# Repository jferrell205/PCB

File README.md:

# PCB
Collection of custom PCBs

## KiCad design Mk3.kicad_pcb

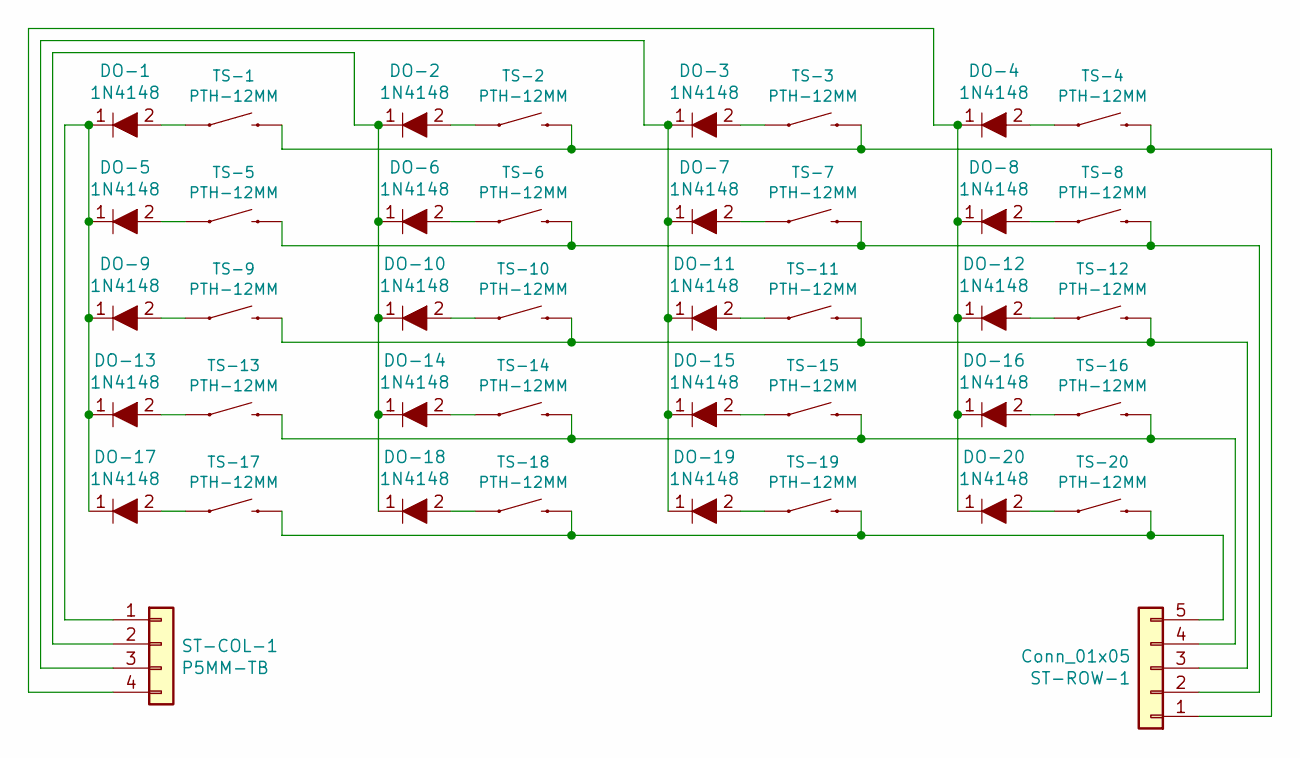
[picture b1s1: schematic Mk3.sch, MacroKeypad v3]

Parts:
DO-1, DO-2, DO-3, DO-4, DO-5, DO-6, DO-7, DO-8, DO-9, DO-10, DO-11, DO-12, DO-13, DO-14, DO-15, DO-16, DO-17, DO-18, DO-19, DO-20: 1N4148; Diode_1N4148_Back; MPN 1N4148; Digi-Key_PN 1N4148FS-ND
ST-COL-1: P5MM-TB; Term_Block_1x4_P5mm
ST-ROW-1: Conn_01x05; Term_Block_1x5_P5mm
TS-1, TS-2, TS-3, TS-4, TS-5, TS-6, TS-7, TS-8, TS-9, TS-10, TS-11, TS-12, TS-13, TS-14, TS-15, TS-16, TS-17, TS-18, TS-19, TS-20: PTH-12MM; TACTILE_SWITCH_PTH_12MM

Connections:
unnamed: DO-1.1, DO-5.1, DO-9.1, DO-13.1, DO-17.1, ST-COL-1.1
unnamed: DO-1.2, TS-1.1
unnamed: DO-2.2, TS-2.1
unnamed: DO-3.2, TS-3.1
unnamed: DO-4.2, TS-4.1
unnamed: DO-5.2, TS-5.1
unnamed: DO-6.2, TS-6.1
unnamed: DO-7.2, TS-7.1
unnamed: DO-8.2, TS-8.1
unnamed: DO-9.2, TS-9.1
unnamed: DO-2.1, DO-6.1, DO-10.1, DO-14.1, DO-18.1, ST-COL-1.2
unnamed: DO-10.2, TS-10.1
unnamed: DO-3.1, DO-7.1, DO-11.1, DO-15.1, DO-19.1, ST-COL-1.3
unnamed: DO-11.2, TS-11.1
unnamed: DO-4.1, DO-8.1, DO-12.1, DO-16.1, DO-20.1, ST-COL-1.4
unnamed: DO-12.2, TS-12.1
unnamed: DO-13.2, TS-13.1
unnamed: DO-14.2, TS-14.1
unnamed: DO-15.2, TS-15.1
unnamed: DO-16.2, TS-16.1
unnamed: DO-17.2, TS-17.1
unnamed: DO-18.2, TS-18.1
unnamed: DO-19.2, TS-19.1
unnamed: DO-20.2, TS-20.1
unnamed: ST-ROW-1.1, TS-1.3 (2), TS-2.3 (2), TS-3.3 (2), TS-4.3 (2)
unnamed: ST-ROW-1.2, TS-5.3 (2), TS-6.3 (2), TS-7.3 (2), TS-8.3 (2)
unnamed: ST-ROW-1.3, TS-9.3 (2), TS-10.3 (2), TS-11.3 (2), TS-12.3 (2)
unnamed: ST-ROW-1.4, TS-13.3 (2), TS-14.3 (2), TS-15.3 (2), TS-16.3 (2)
unnamed: ST-ROW-1.5, TS-17.3 (2), TS-18.3 (2), TS-19.3 (2), TS-20.3 (2)

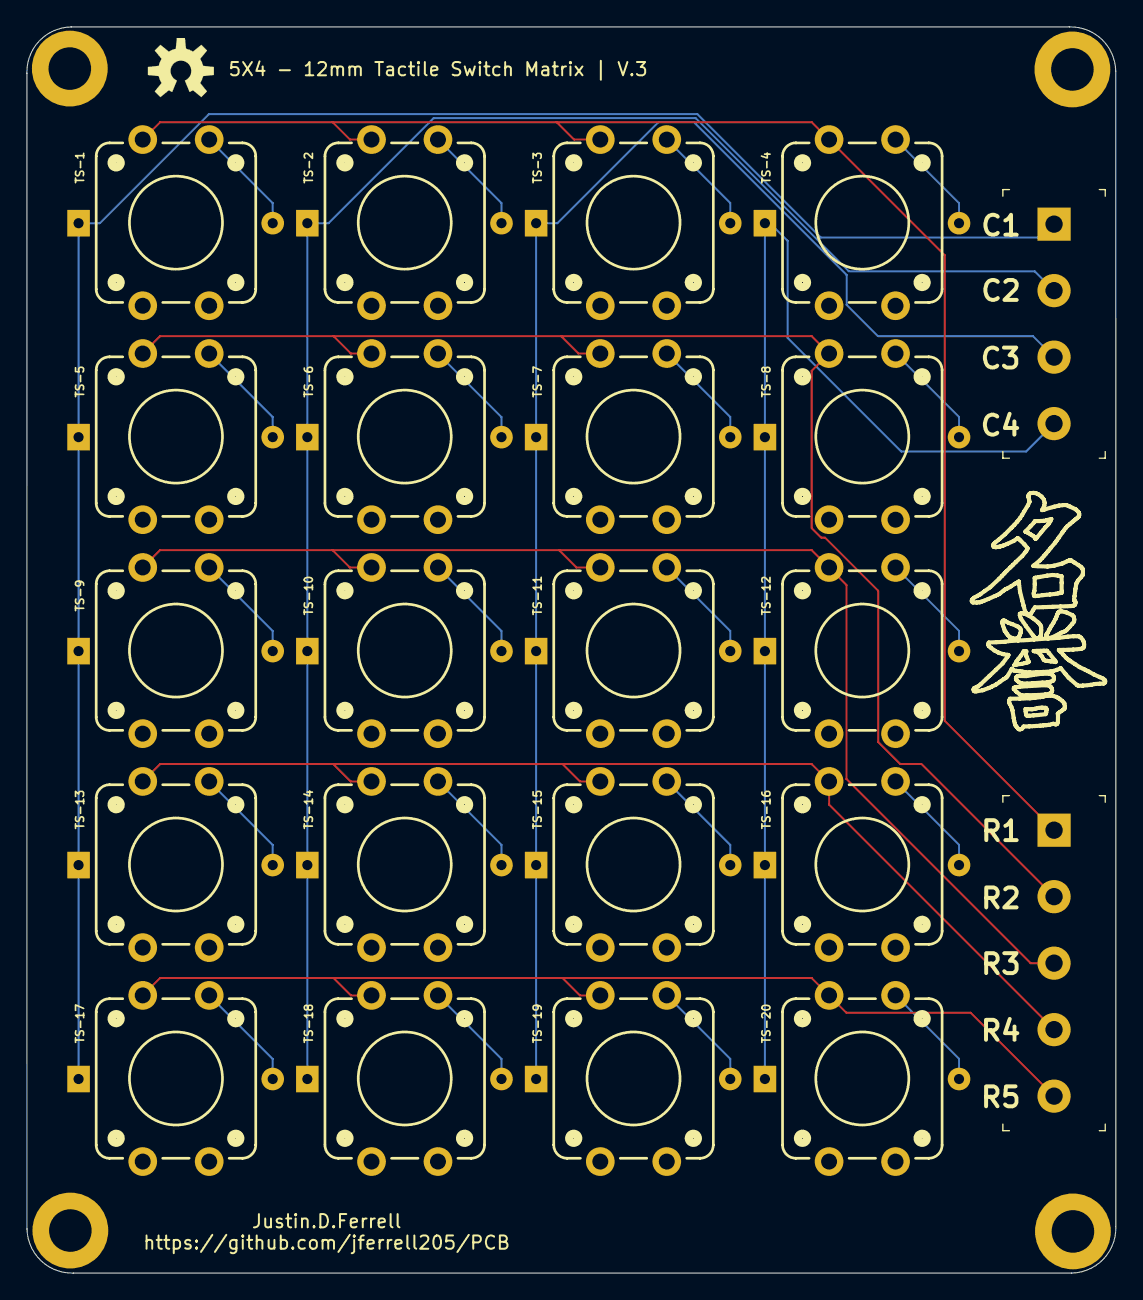
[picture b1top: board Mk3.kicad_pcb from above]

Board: 2 copper layers, 81.9 x 93.7 mm, 42 parts (0 on the bottom side), 29 nets.

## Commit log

2021-10-20 Add files via upload
    5x4 Macro Keypad Matrix
2021-10-20 Add files via upload
    5x4 - 12MM Tactile Switch Keypad Matrix
